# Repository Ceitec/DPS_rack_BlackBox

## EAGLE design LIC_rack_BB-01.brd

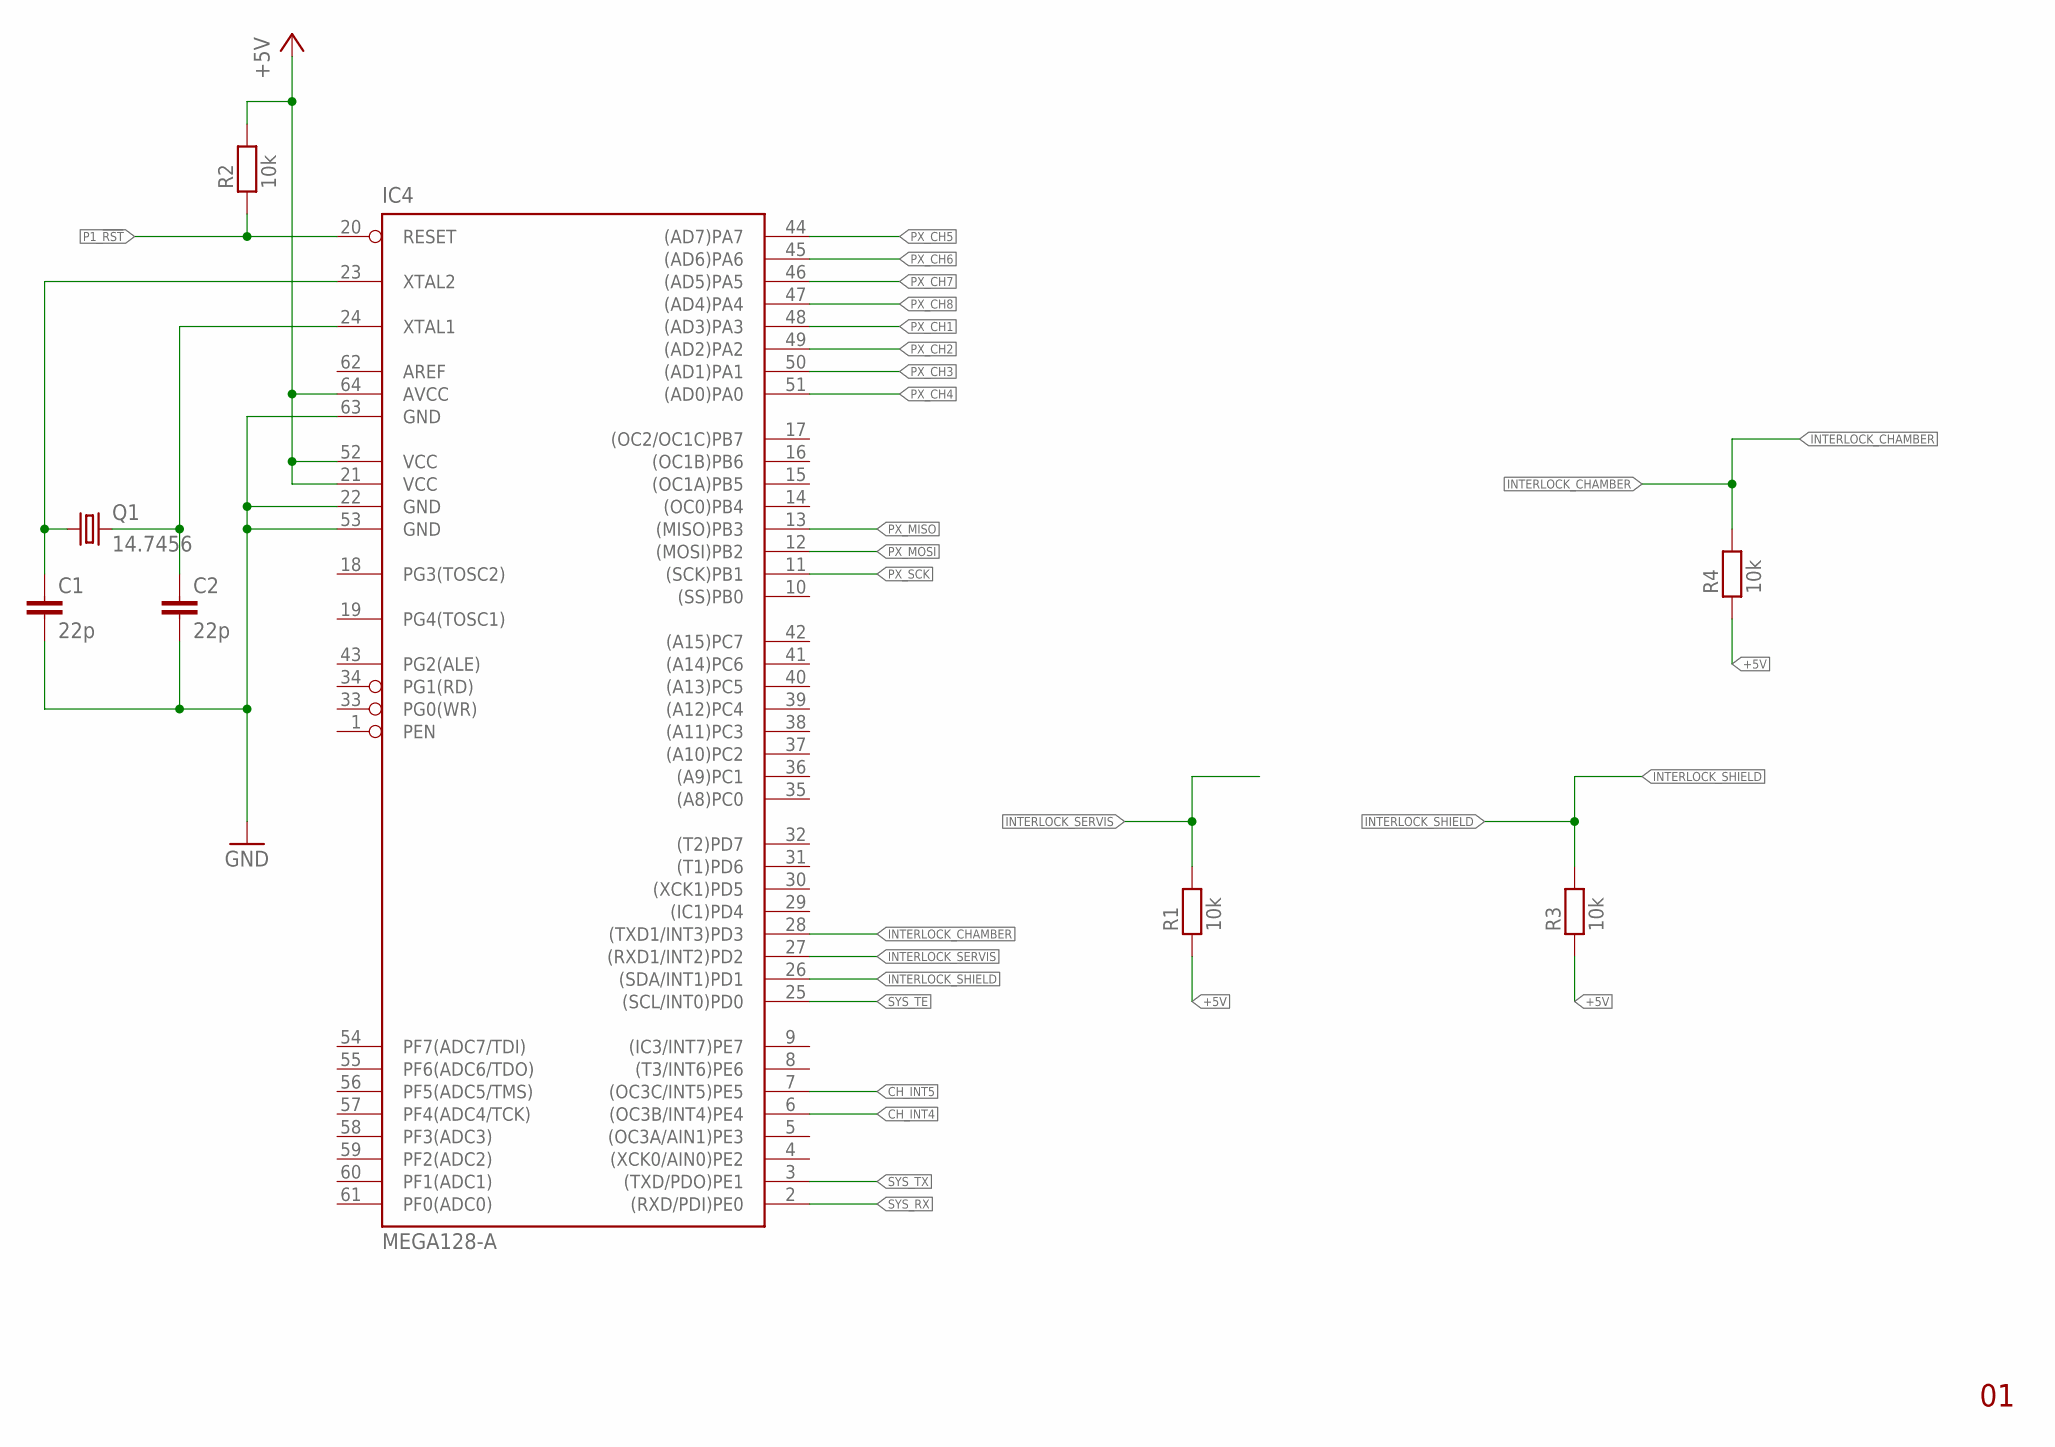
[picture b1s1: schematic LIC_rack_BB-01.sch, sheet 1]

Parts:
C1, C2: 22p; C0805
IC4: MEGA128-A; TQFP64
Q1: 14.7456; HC49U70
R1, R2, R3, R4: 10k; 1206

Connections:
+5V: IC4.21 (VCC), IC4.52 (VCC), IC4.64 (AVCC), R1.1, R2.2, R3.1, R4.1; also elsewhere on the board
CH_INT4: IC4.6 ((OC3B/INT4)PE4); also elsewhere on the board
CH_INT5: IC4.7 ((OC3C/INT5)PE5); also elsewhere on the board
CLK1: C1.1, IC4.23 (XTAL2), Q1.1
GND: C1.2, C2.2, IC4.22 (GND), IC4.53 (GND), IC4.63 (GND); also elsewhere on the board
INTERLOCK_CHAMBER: IC4.28 ((TXD1/INT3)PD3), R4.2; also elsewhere on the board
INTERLOCK_SERVIS: IC4.27 ((RXD1/INT2)PD2), R1.2; also elsewhere on the board
INTERLOCK_SHIELD: IC4.26 ((SDA/INT1)PD1), R3.2; also elsewhere on the board
unnamed: C2.1, IC4.24 (XTAL1), Q1.2
P1_!RST: IC4.20 (RESET), R2.1; also elsewhere on the board
PX_CH1: IC4.48 ((AD3)PA3); also elsewhere on the board
PX_CH2: IC4.49 ((AD2)PA2); also elsewhere on the board
PX_CH3: IC4.50 ((AD1)PA1); also elsewhere on the board
PX_CH4: IC4.51 ((AD0)PA0); also elsewhere on the board
PX_CH5: IC4.44 ((AD7)PA7); also elsewhere on the board
PX_CH6: IC4.45 ((AD6)PA6)
PX_CH7: IC4.46 ((AD5)PA5)
PX_CH8: IC4.47 ((AD4)PA4)
PX_MISO: IC4.13 ((MISO)PB3)
PX_MOSI: IC4.12 ((MOSI)PB2)
PX_SCK: IC4.11 ((SCK)PB1); also elsewhere on the board
SYS_RX: IC4.2 ((RXD/PDI)PE0); also elsewhere on the board
SYS_TE: IC4.25 ((SCL/INT0)PD0); also elsewhere on the board
SYS_TX: IC4.3 ((TXD/PDO)PE1); also elsewhere on the board

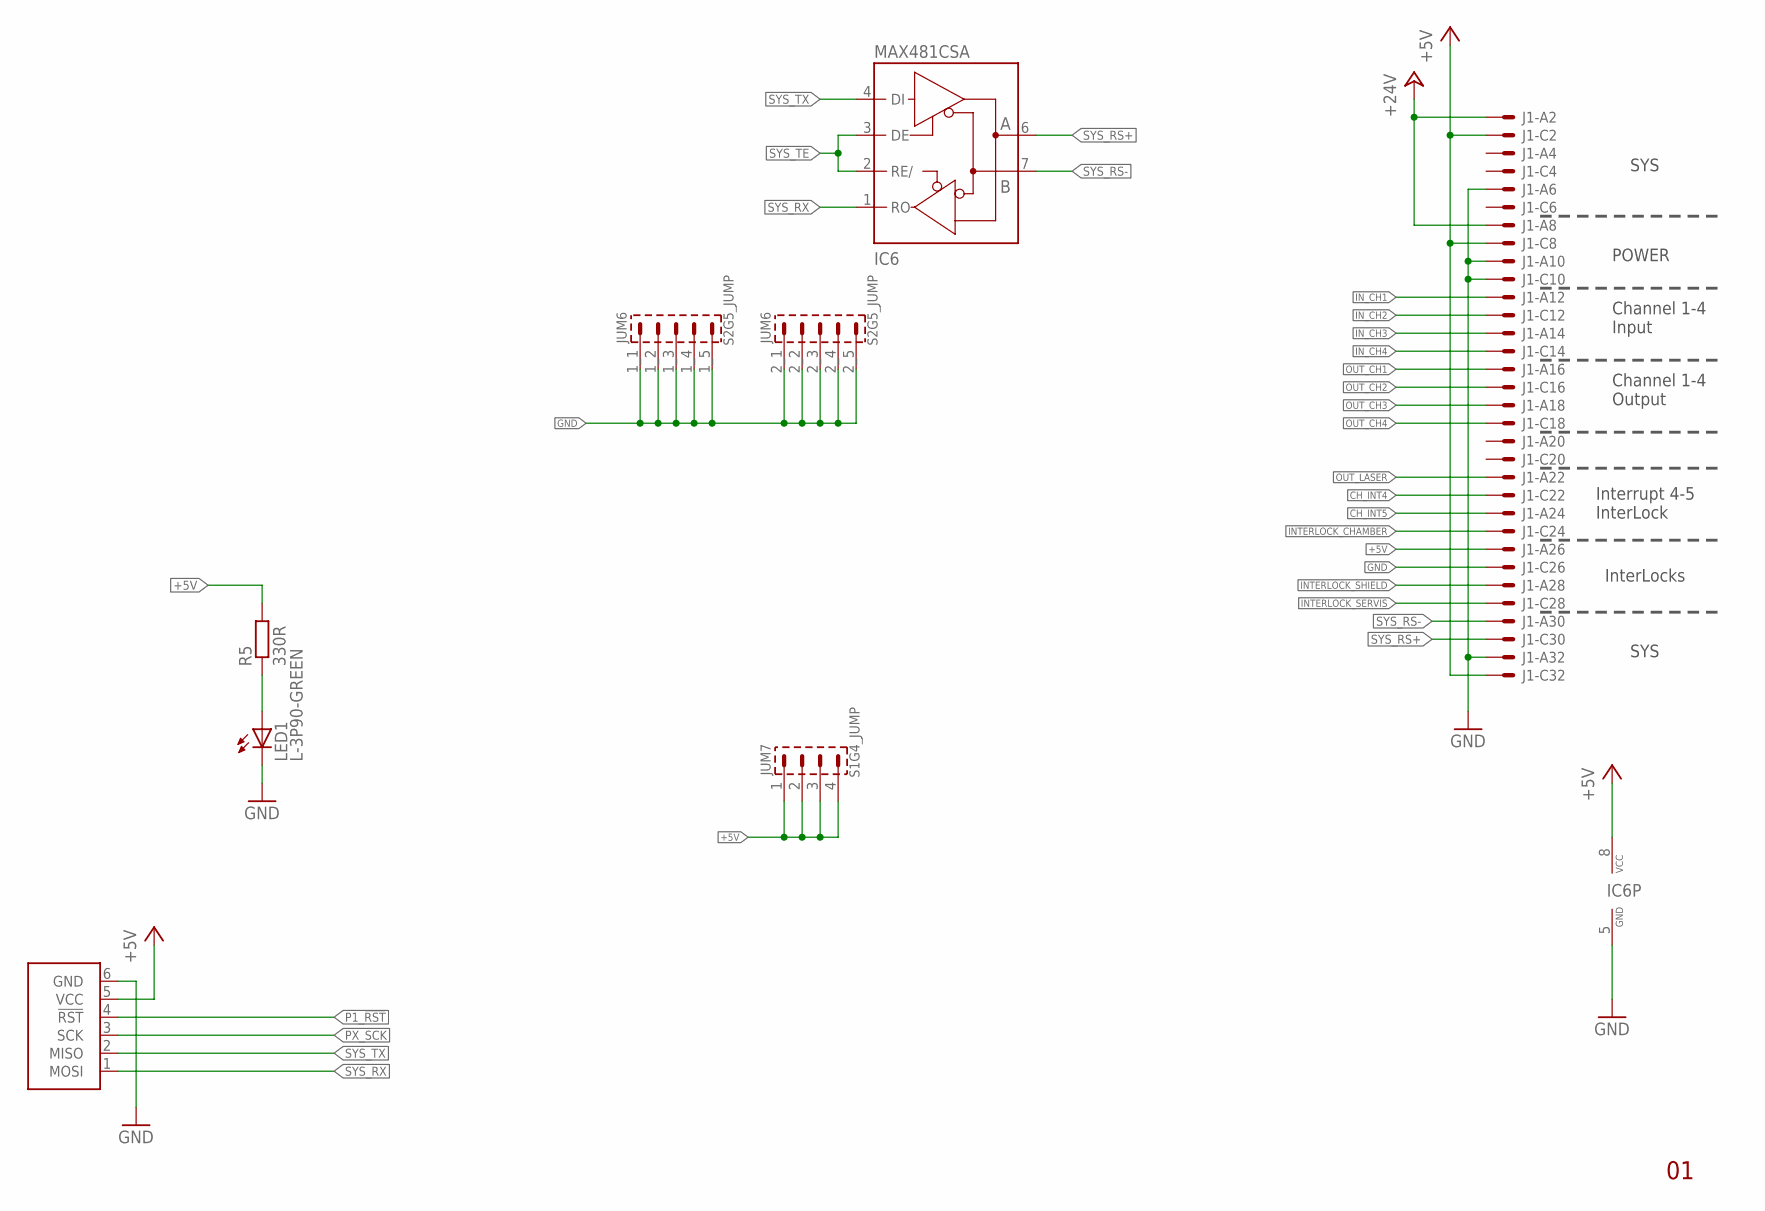
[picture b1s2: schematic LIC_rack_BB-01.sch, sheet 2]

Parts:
IC6: MAX481CSA; SO08
J1: VG32SP; VG32P
JUM6: S2G5_JUMP; S2G5_JUM
JUM7: S1G4_JUMP; S1G4_JUM
LED1: L-3P90-GREEN; L-3P90
R5: 330R; R1206
U1: ATPROG-V; 6410-06

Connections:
+5V: IC6.8 (VCC), J1.A26 (MS), J1.C2 (MS), J1.C8 (MS), J1.C32 (MSV), JUM7.1, JUM7.2, JUM7.3, JUM7.4, R5.2, U1.5 (VCC); also elsewhere on the board
+24V: J1.A2 (MS), J1.A8 (MS)
CH_INT4: J1.C22 (MS); also elsewhere on the board
CH_INT5: J1.A24 (MS); also elsewhere on the board
GND: IC6.5 (GND), J1.A6 (MS), J1.A10 (MS), J1.A32 (MS), J1.C10 (MS), J1.C26 (MS), JUM6.1_1 (1), JUM6.1_2 (2), JUM6.1_3 (3), JUM6.1_4 (4), JUM6.1_5 (5), JUM6.2_1 (1), JUM6.2_2 (2), JUM6.2_3 (3), JUM6.2_4 (4), JUM6.2_5 (5), LED1.K (C), U1.6 (GND); also elsewhere on the board
INTERLOCK_CHAMBER: J1.C24 (MS); also elsewhere on the board
INTERLOCK_SERVIS: J1.C28 (MS); also elsewhere on the board
INTERLOCK_SHIELD: J1.A28 (MS); also elsewhere on the board
IN_CH1: J1.A12 (MS); also elsewhere on the board
IN_CH2: J1.C12 (MS); also elsewhere on the board
IN_CH3: J1.A14 (MS); also elsewhere on the board
IN_CH4: J1.C14 (MS); also elsewhere on the board
unnamed: LED1.A, R5.1
OUT_CH1: J1.A16 (MS); also elsewhere on the board
OUT_CH2: J1.C16 (MS); also elsewhere on the board
OUT_CH3: J1.A18 (MS); also elsewhere on the board
OUT_CH4: J1.C18 (MS); also elsewhere on the board
OUT_LASER: J1.A22 (MS); also elsewhere on the board
P1_!RST: U1.4 (!RST); also elsewhere on the board
PX_SCK: U1.3 (SCK); also elsewhere on the board
SYS_RS+: IC6.6 (A), J1.C30 (MS)
SYS_RS-: IC6.7 (B), J1.A30 (MS)
SYS_RX: IC6.1 (RO), U1.1 (MOSI); also elsewhere on the board
SYS_TE: IC6.2 (RE/), IC6.3 (DE); also elsewhere on the board
SYS_TX: IC6.4 (DI), U1.2 (MISO); also elsewhere on the board

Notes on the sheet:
SYS
POWER
Channel 1-4 Input
Channel 1-4 Output
Interrupt 4-5 InterLock
InterLocks

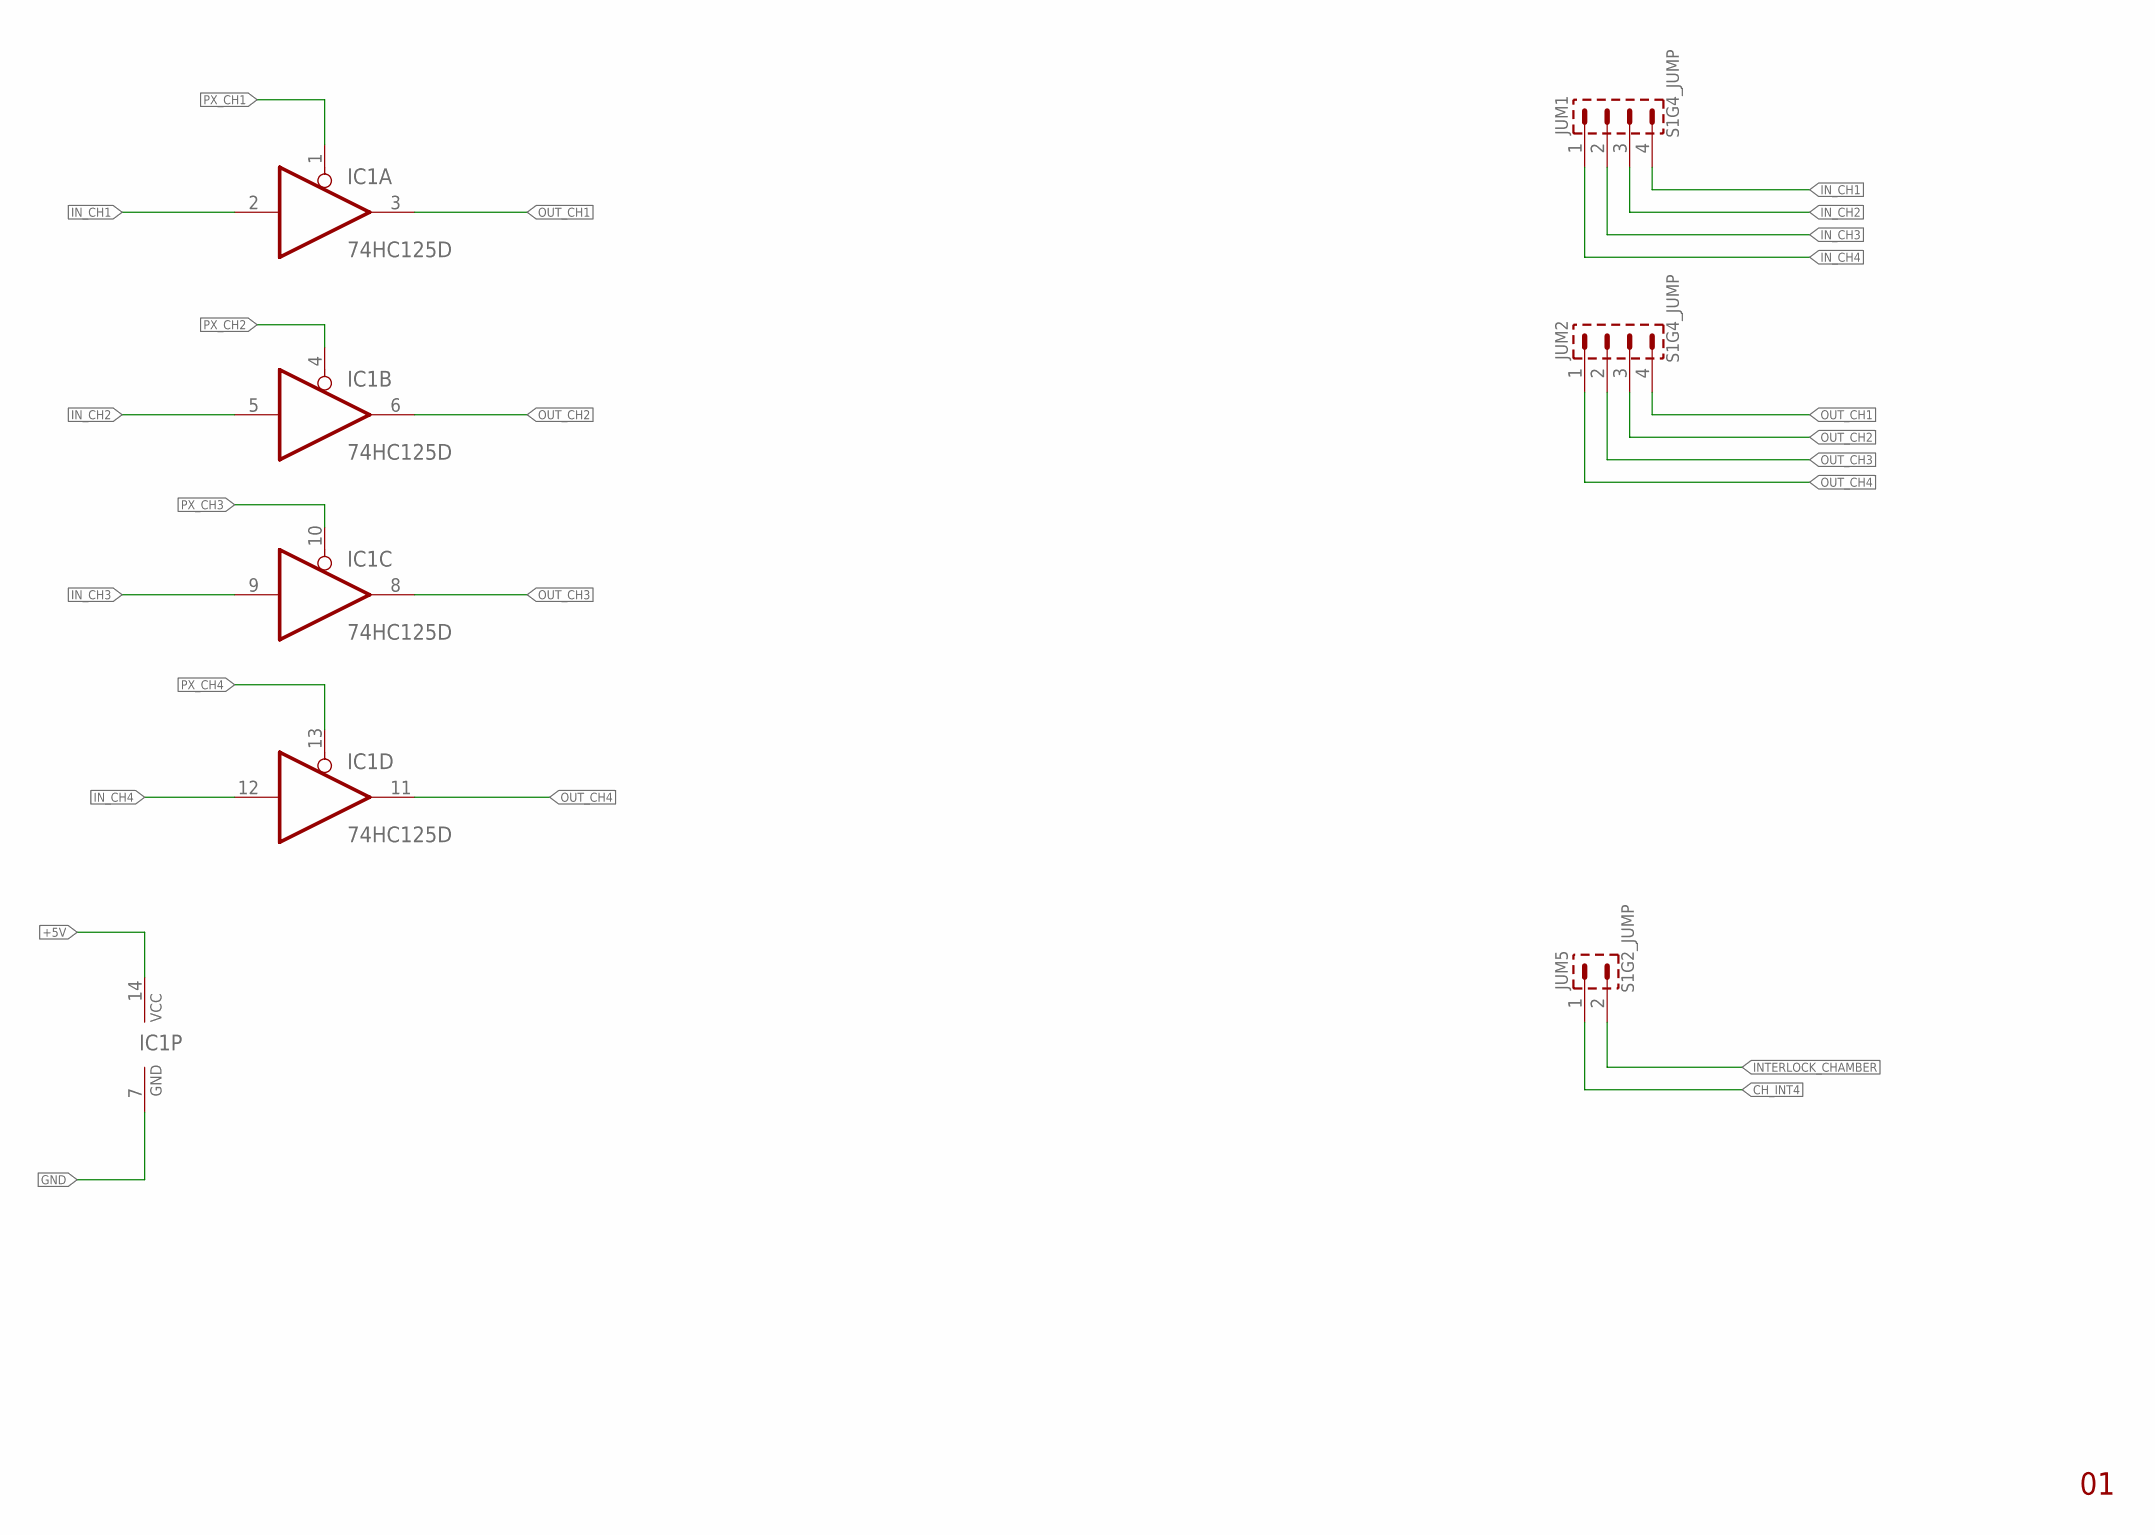
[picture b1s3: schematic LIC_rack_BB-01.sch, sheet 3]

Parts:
IC1: 74HC125D; SO14
JUM1, JUM2: S1G4_JUMP; S1G4_JUM
JUM5: S1G2_JUMP; S1G2_JUM

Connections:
+5V: IC1.14 (VCC); also elsewhere on the board
CH_INT4: JUM5.1; also elsewhere on the board
GND: IC1.7 (GND); also elsewhere on the board
INTERLOCK_CHAMBER: JUM5.2; also elsewhere on the board
IN_CH1: IC1.2 (I), JUM1.4; also elsewhere on the board
IN_CH2: IC1.5 (I), JUM1.3; also elsewhere on the board
IN_CH3: IC1.9 (I), JUM1.2; also elsewhere on the board
IN_CH4: IC1.12 (I), JUM1.1; also elsewhere on the board
OUT_CH1: IC1.3 (O), JUM2.4; also elsewhere on the board
OUT_CH2: IC1.6 (O), JUM2.3; also elsewhere on the board
OUT_CH3: IC1.8 (O), JUM2.2; also elsewhere on the board
OUT_CH4: IC1.11 (O), JUM2.1; also elsewhere on the board
PX_CH1: IC1.1 (OE); also elsewhere on the board
PX_CH2: IC1.4 (OE); also elsewhere on the board
PX_CH3: IC1.10 (OE); also elsewhere on the board
PX_CH4: IC1.13 (OE); also elsewhere on the board

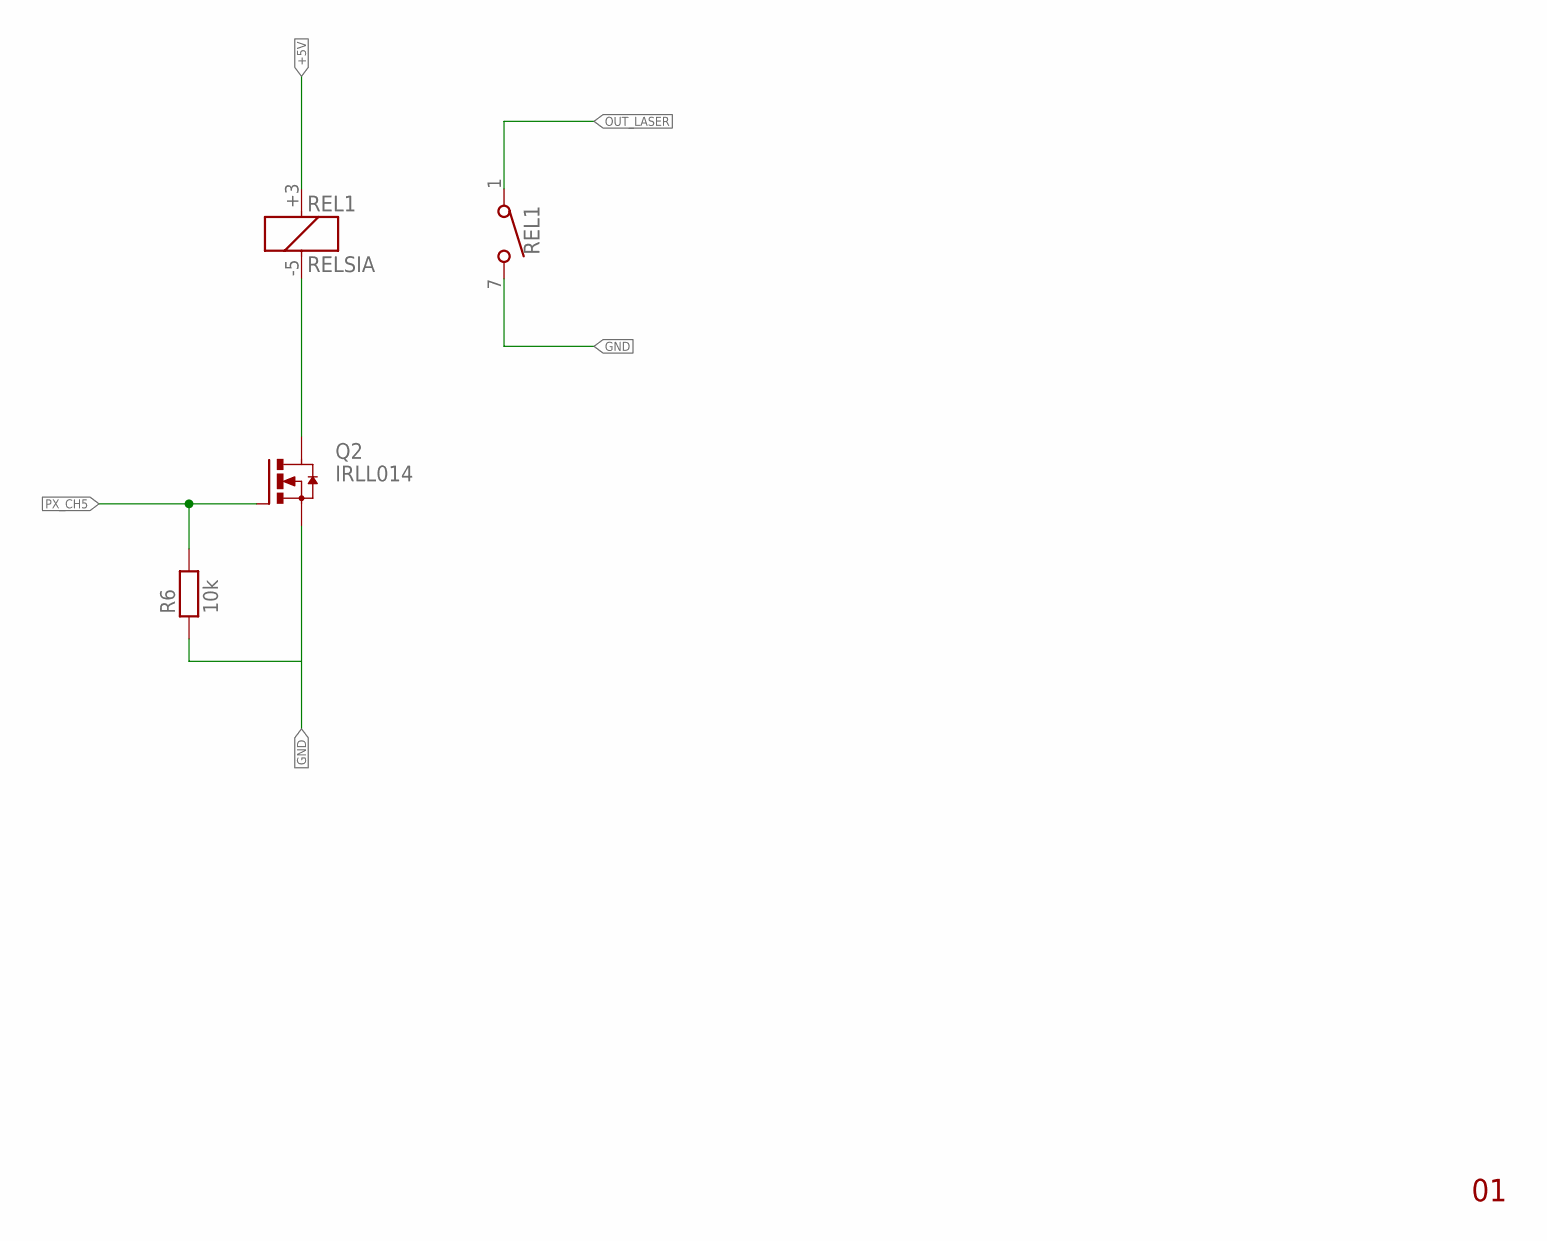
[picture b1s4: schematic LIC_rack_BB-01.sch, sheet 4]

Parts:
Q2: IRLL014; SOT223
R6: 10k; 1206
REL1: RELSIA

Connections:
+5V: REL1.+3 (C+); also elsewhere on the board
GND: Q2.3 (S), R6.1, REL1.7 (2); also elsewhere on the board
unnamed: Q2.2 (D), Q2.4 (D), REL1.-5 (C-)
OUT_LASER: REL1.1; also elsewhere on the board
PX_CH5: Q2.1 (G), R6.2; also elsewhere on the board

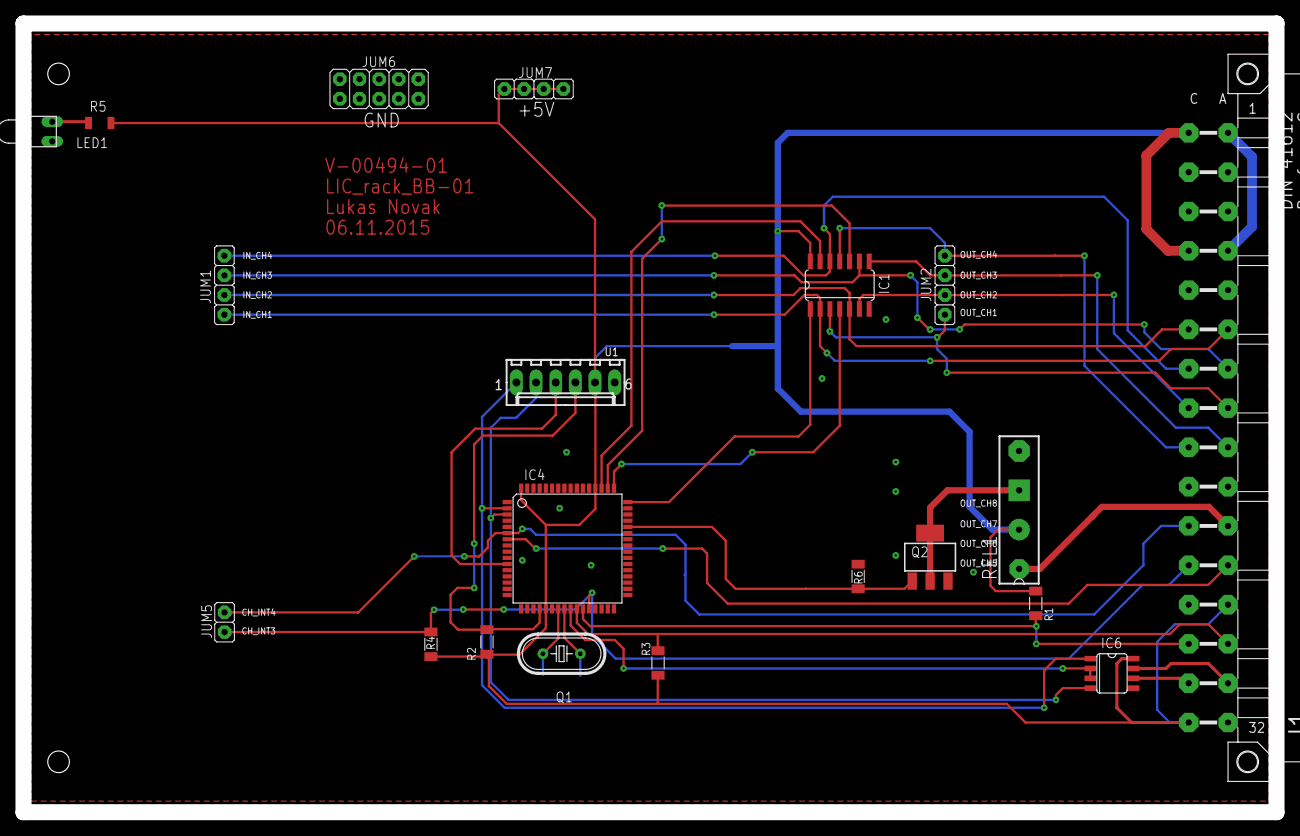
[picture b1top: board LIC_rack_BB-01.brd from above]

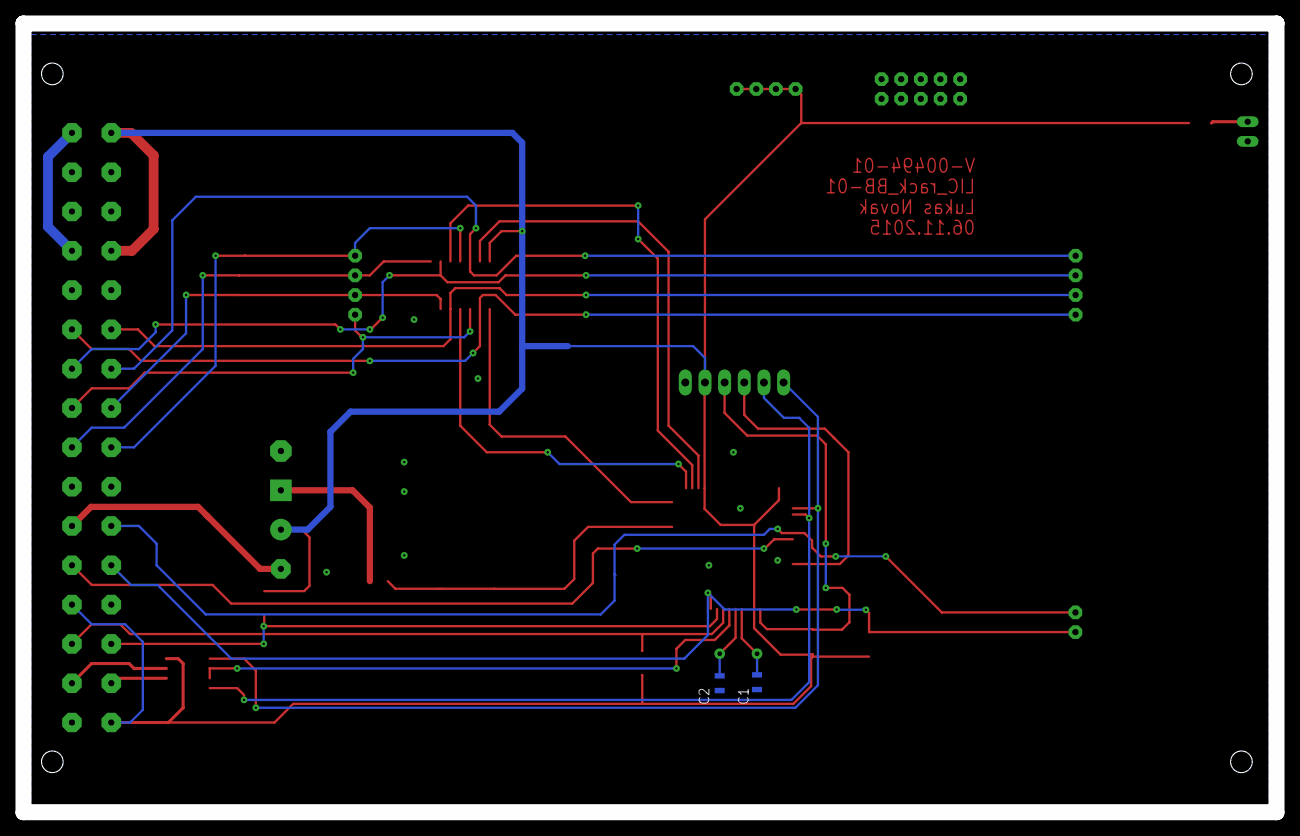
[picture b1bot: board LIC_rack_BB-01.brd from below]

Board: 2 copper layers, 162.0 x 102.0 mm, 22 parts (2 on the bottom side), 33 nets.

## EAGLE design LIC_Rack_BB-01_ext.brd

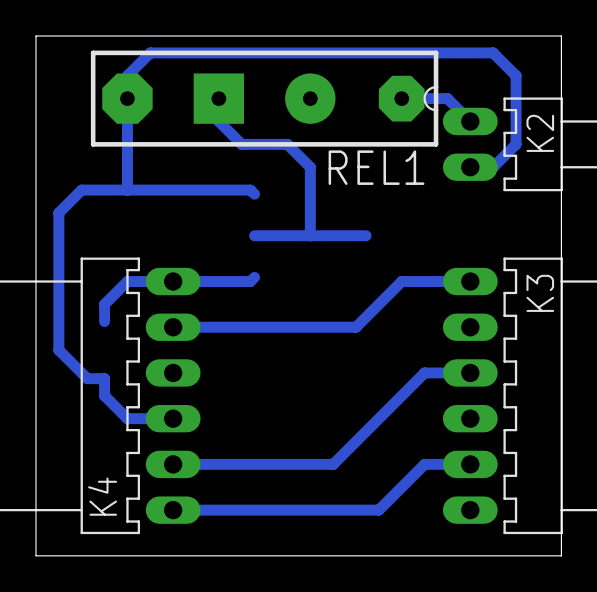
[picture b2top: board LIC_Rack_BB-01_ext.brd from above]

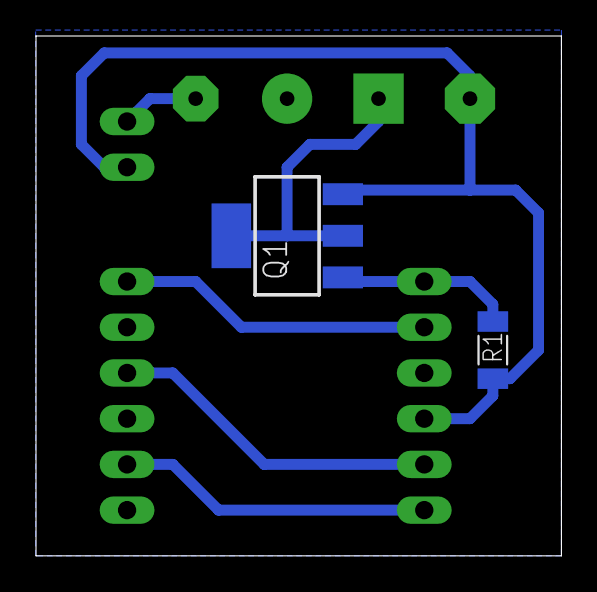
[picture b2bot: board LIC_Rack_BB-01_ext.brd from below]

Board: 2 copper layers, 29.2 x 28.9 mm, 6 parts (2 on the bottom side), 8 nets.

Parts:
K2: PSH02-02W
K3, K4: PSH02-06W
Q1: IRLL014; SOT223
R1: 10k; 1206
REL1: RELSIA?; RELSIA

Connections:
+5V: K4.4, REL1.+3
GND: K2.2, K3.2, K3.4, K3.6, K4.3, Q1.3, R1.1, REL1.7
INTERLOCK_CHAMBER: K3.1, K4.5
INTERLOCK_SERVIS: K3.5, K4.1
INTERLOCK_SHIELD: K3.3, K4.2
IN_LASER: K2.1, REL1.1
unnamed: Q1.2, Q1.4, REL1.-5
PA7: K4.6, Q1.1, R1.2

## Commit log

2015-08-11 :lollipop: Added .gitattributes & .gitignore files
2015-08-11 BlackBox
2015-08-11 Pridani zakazanych koncovek
2015-08-12 Nová externí deska
    Je potřeba dodělat externí desku s relátkem
2015-08-19 Pridan
    Pridan pouze obrazek desky pro vyrobu
2015-09-16 Upravy
2015-11-10 Pridána nová verze
    Přidána nová verze zkráceno na 4 In a 4 Out a přidáno relé na desku
2015-11-10 Opraveno
    Opraveno

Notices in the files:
parts and their libraries:
Copyright (C) PaJa 2011-2014
Copyright (C) PaJa 2001-2014
